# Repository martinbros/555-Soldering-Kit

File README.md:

# 555 Soldering Kit
 555 Timer Soldering Kit

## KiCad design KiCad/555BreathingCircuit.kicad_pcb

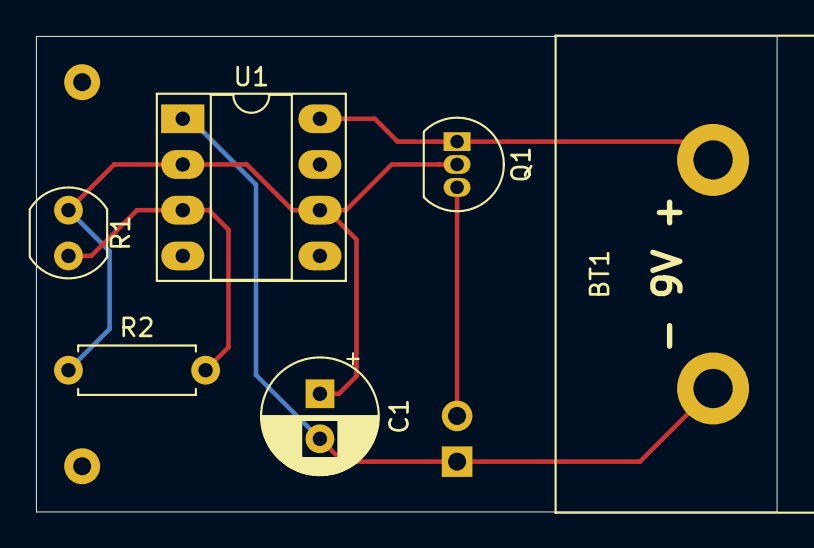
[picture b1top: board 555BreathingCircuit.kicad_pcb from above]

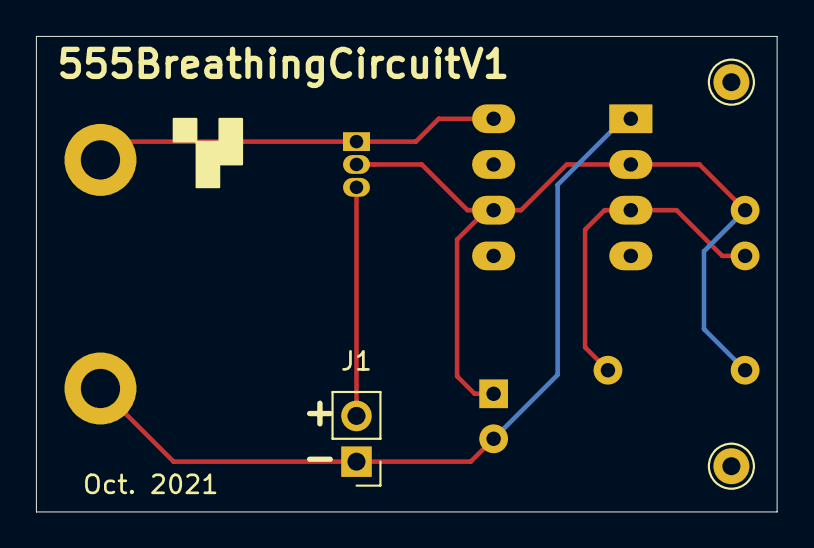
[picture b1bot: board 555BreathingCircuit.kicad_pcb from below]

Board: 2 copper layers, 41.1 x 26.4 mm, 9 parts (3 on the bottom side), 5 nets.

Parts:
BT1: Battery_Cell; 9V_Batt_Clip
C1: 470u; CP_Radial_D6.3mm_P2.50mm
H1, H2: MountingHole_Pad; Pin_D1.0mm_L10.0mm
J1: Conn_01x02_Female; PinHeader_1x02_P2.54mm_Vertical
Q1: BC547; TO-92_Inline
R1: A1050; R_LDR_4.9x4.2mm_P2.54mm_Vertical
R2: 16k; R_Axial_DIN0207_L6.3mm_D2.5mm_P7.62mm_Horizontal
U1: NE555; DIP-8_W7.62mm_Socket_LongPads

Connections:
+9V: BT1.1, Q1.1, U1.8
GND: BT1.2, C1.2, J1.1, U1.1
unnamed: C1.1, Q1.2, R1.1, R2.1, U1.2, U1.6
unnamed: J1.2, Q1.3
unnamed: R1.2, R2.2, U1.3

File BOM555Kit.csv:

Symbol,Value,Mouser PN
BT1,~,534-968
C1,470u,80-A750EQ477M1CAAE15
U1,555,926-LMC555CN/N0PB
R1,~,Personal Stock
R2,16k,594-5063JD16K00F
Q1,BC547,512-BC547BTF

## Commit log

2025-01-23 Adding License
